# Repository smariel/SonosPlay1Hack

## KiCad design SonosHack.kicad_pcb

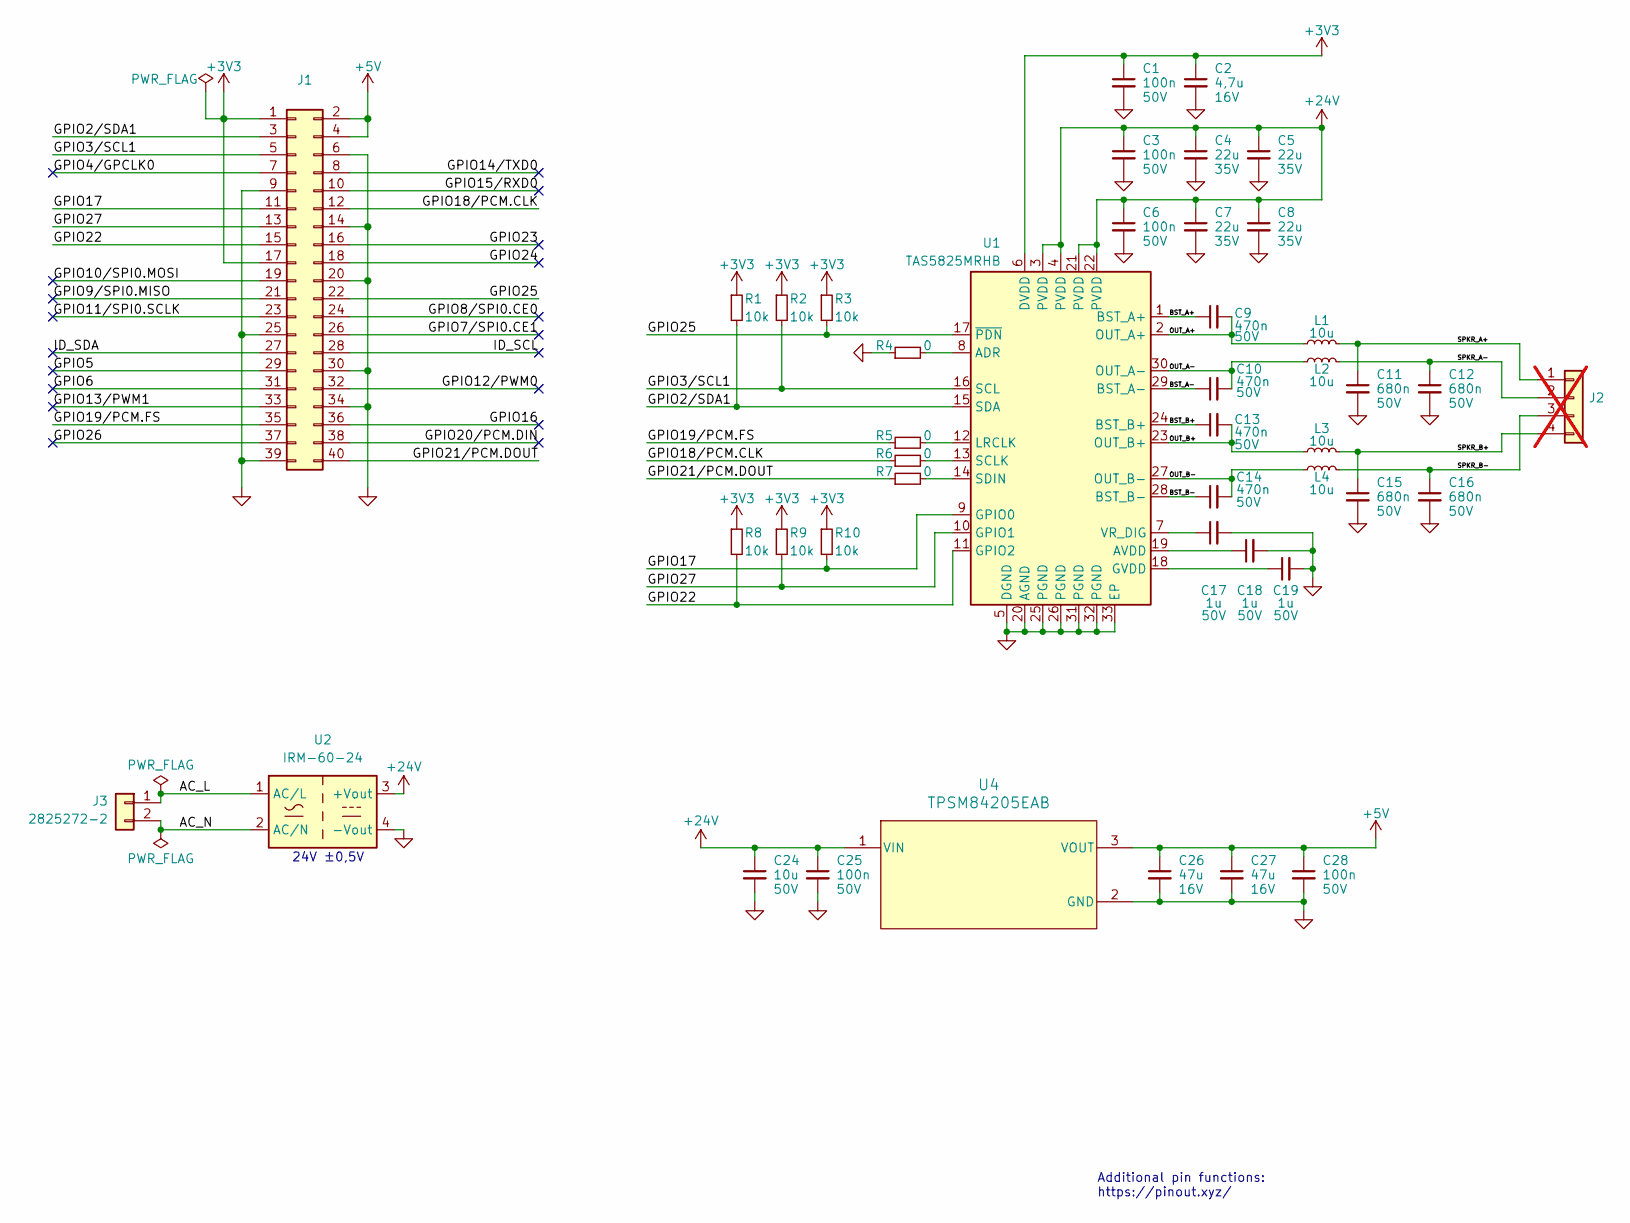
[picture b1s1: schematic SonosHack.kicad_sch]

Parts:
C1, C3, C6, C25, C28: 100n; C_0402_1005Metric; Voltage 50V; Part Number GRM155R71H104KE14D; LCSC C77020
C2: 4,7u; C_0603_1608Metric; Voltage 16V; Part Number GRM188Z71C475KE21D; LCSC C389010
C4, C5, C7, C8: 22u; C_0805_2012Metric; Voltage 35V; Part Number C2012X5R1V226MT000E; LCSC C338080
C9, C10, C13, C14: 470n; C_0603_1608Metric; Voltage 50V; Part Number CC0603KRX7R9BB474; LCSC C513577
C11, C12, C15, C16: 680n; C_0805_2012Metric; Voltage 50V; Part Number CC0805KKX7R9BB684; LCSC C107133
C17, C18, C19: 1u; C_0603_1608Metric; Voltage 50V; Part Number CL10B105KB8NQNC; LCSC C5199872
C24: 10u; C_1206_3216Metric; Voltage 50V; Part Number GRM31CR61H106KA12L; LCSC C77092
C26, C27: 47u; C_1206_3216Metric; Voltage 16V; Part Number EMK316BBJ476ML-T; LCSC C385907
J1: PinSocket_2x20_P2.54mm_Vertical; Part Number 2.54-2*20; LCSC C2977589
J2: ?; PinHeader_1x04_P2.00mm_Vertical; not fitted
J3: 2825272-2; Part Number 2825272-2; LCSC C17180232
L1, L2, L3, L4: 10u; 1274ASH100MP3; Part Number 1274AS-H-100M=P3; LCSC C2047495
R1, R2, R3, R8, R9, R10: 10k; R_0402_1005Metric; Part Number RC0402FR-0710KL; LCSC C60490
R4, R5, R6, R7: 0; R_0402_1005Metric; Part Number RC0402FR-070RL; LCSC C106231
U1: TAS5825MRHB; Texas_RHB0032E_VQFN-32-1EP_5x5mm_P0.5mm_EP3.45x3.45mm_Therm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; Part Number TAS5825MRHB; LCSC C471049
U2: IRM-60-24; Converter_ACDC_MeanWell_IRM-60-xx_THT; Part Number IRM-90-24; LCSC C5656554
U4: TPSM84205EAB; EAB0003A; Part Number TPSM84205EAB; LCSC C2870509

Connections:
+3V3: C1.1, C2.1, J1.1, J1.17, R1.1, R2.1, R3.1, R8.1, R9.1, R10.1, U1.6 (DVDD)
+5V: C26.1, C27.1, C28.1, J1.2, J1.4, U4.3 (VOUT)
+24V: C3.1, C4.1, C5.1, C6.1, C7.1, C8.1, C24.1, C25.1, U1.3 (PVDD), U1.4 (PVDD), U1.21 (PVDD), U1.22 (PVDD), U2.3 (+Vout), U4.1 (VIN)
/AC_L: J3.1, U2.1 (AC/L)
/AC_N: J3.2, U2.2 (AC/N)
/BST_A+: C9.1, U1.1 (BST_A+)
/BST_A-: C10.1, U1.29 (BST_A-)
/BST_B+: C13.1, U1.24 (BST_B+)
/BST_B-: C14.1, U1.28 (BST_B-)
/GPIO2/SDA1: J1.3, R1.2, U1.15 (SDA)
/GPIO3/SCL1: J1.5, R2.2, U1.16 (SCL)
/GPIO4/GPCLK0: J1.7
/GPIO5: J1.29
/GPIO6: J1.31
/GPIO7/SPI0.CE1: J1.26
/GPIO8/SPI0.CE0: J1.24
/GPIO9/SPI0.MISO: J1.21
/GPIO10/SPI0.MOSI: J1.19
/GPIO11/SPI0.SCLK: J1.23
/GPIO12/PWM0: J1.32
/GPIO13/PWM1: J1.33
/GPIO14/TXD0: J1.8
/GPIO15/RXD0: J1.10
/GPIO16: J1.36
/GPIO17: J1.11, R10.2, U1.9 (GPIO0)
/GPIO18/PCM.CLK: J1.12, R6.1
/GPIO19/PCM.FS: J1.35, R5.1
/GPIO20/PCM.DIN: J1.38
/GPIO21/PCM.DOUT: J1.40, R7.1
/GPIO22: J1.15, R8.2, U1.11 (GPIO2)
/GPIO23: J1.16
/GPIO24: J1.18
/GPIO25: J1.22, R3.2, U1.17 (~PDN)
/GPIO26: J1.37
/GPIO27: J1.13, R9.2, U1.10 (GPIO1)
/ID_SCL: J1.28
/ID_SDA: J1.27
/OUT_A+: C9.2, L1.1, U1.2 (OUT_A+)
/OUT_A-: C10.2, L2.1, U1.30 (OUT_A-)
/OUT_B+: C13.2, L3.1, U1.23 (OUT_B+)
/OUT_B-: C14.2, L4.1, U1.27 (OUT_B-)
/SPKR_A+: C11.1, J2.1, L1.2
/SPKR_A-: C12.1, J2.2, L2.2
/SPKR_B+: C15.1, J2.4, L3.2
/SPKR_B-: C16.1, J2.3, L4.2
GND: C1.2, C2.2, C3.2, C4.2, C5.2, C6.2, C7.2, C8.2, C11.2, C12.2, C15.2, C16.2, C17.2, C18.2, C19.2, C24.2, C25.2, C26.2, C27.2, C28.2, J1.6, J1.9, J1.14, J1.20, J1.25, J1.30, J1.34, J1.39, R4.1, U1.5 (DGND), U1.20 (AGND), U1.25 (PGND), U1.26 (PGND), U1.31 (PGND), U1.32 (PGND), U1.33 (EP), U2.4 (-Vout), U4.2 (GND)
unnamed: R4.2, U1.8 (ADR)
unnamed: C18.1, U1.19 (AVDD)
unnamed: C19.1, U1.18 (GVDD)
unnamed: R5.2, U1.12 (LRCLK)
unnamed: R6.2, U1.13 (SCLK)
unnamed: R7.2, U1.14 (SDIN)
unnamed: C17.1, U1.7 (VR_DIG)

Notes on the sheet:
24V ±0,5V
Additional pin functions: https://pinout.xyz/

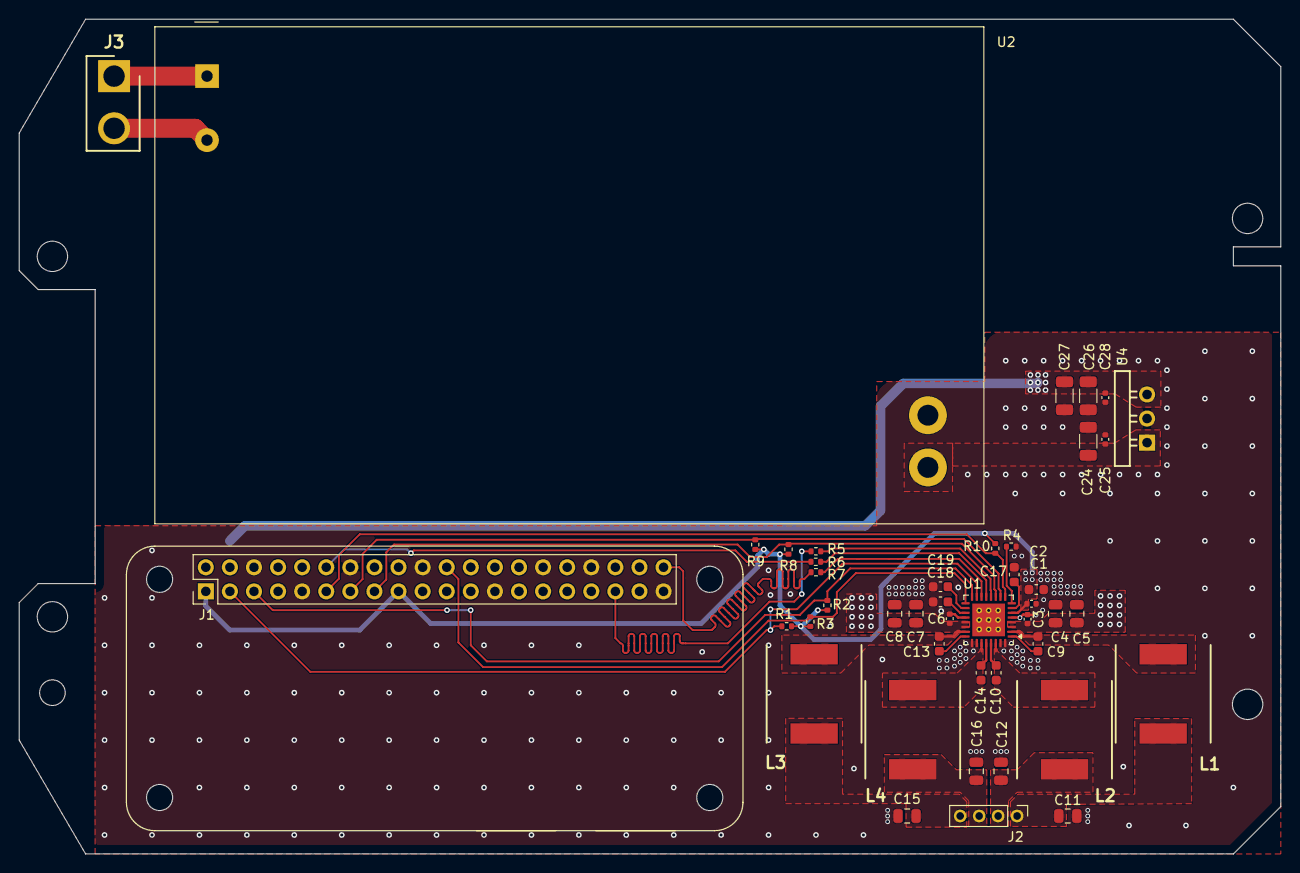
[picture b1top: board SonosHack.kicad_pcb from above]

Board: 2 copper layers, 133.0 x 88.0 mm, 45 parts (0 on the bottom side), 34 nets.

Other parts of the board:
J4: RPI; RASPBERRYPI-ZERO_RPI-ZERO
